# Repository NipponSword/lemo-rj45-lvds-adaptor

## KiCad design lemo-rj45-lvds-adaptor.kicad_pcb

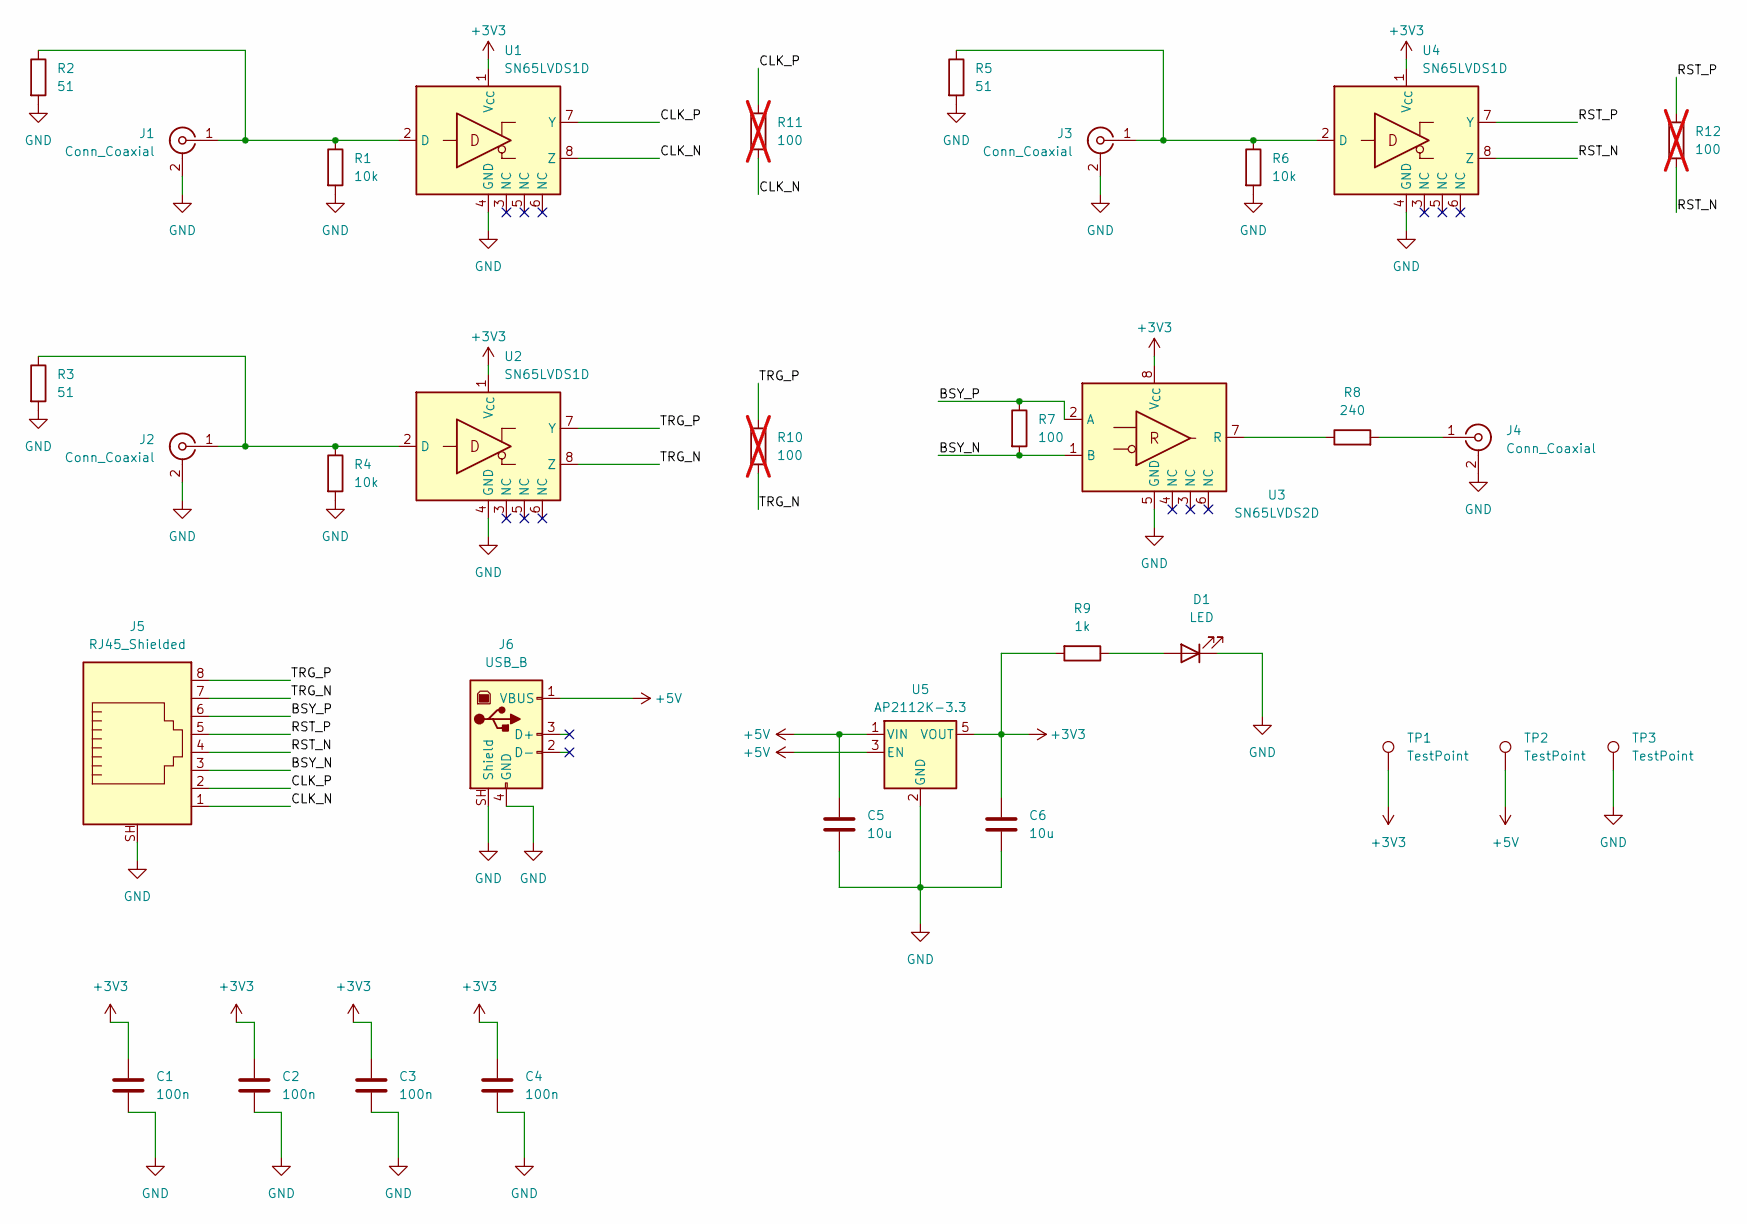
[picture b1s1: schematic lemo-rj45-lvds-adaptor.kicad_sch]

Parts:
C1, C2, C3, C4: 100n; C_0805_2012Metric_Pad1.18x1.45mm_HandSolder
C5, C6: 10u; C_0805_2012Metric_Pad1.18x1.45mm_HandSolder
D1: LED; LED_0805_2012Metric_Pad1.15x1.40mm_HandSolder
J1, J2, J3, J4: Conn_Coaxial; HS_85_QLA-01-0-2_ML97_RightAngle
J5: RJ45_Shielded; RJ45_Amphenol_RJHSE5380
J6: USB_B; USB_B_OST_USB-B1HSxx_Horizontal
R1, R4, R6: 10k; R_0805_2012Metric_Pad1.20x1.40mm_HandSolder
R2, R3, R5: 51; R_1206_3216Metric_Pad1.30x1.75mm_HandSolder
R7: 100; R_0805_2012Metric_Pad1.20x1.40mm_HandSolder
R8: 240; R_0805_2012Metric_Pad1.20x1.40mm_HandSolder
R9: 1k; R_0805_2012Metric_Pad1.20x1.40mm_HandSolder
R10, R11, R12: 100; R_0805_2012Metric_Pad1.20x1.40mm_HandSolder; not fitted
TP1, TP2, TP3: TestPoint; TestPoint_THTPad_D2.0mm_Drill1.0mm
U1, U2, U4: SN65LVDS1D; SOIC-8_3.9x4.9mm_P1.27mm
U3: SN65LVDS2D; SOIC-8_3.9x4.9mm_P1.27mm
U5: AP2112K-3.3; SOT-23-5

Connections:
+3V3: C1.1, C2.1, C3.1, C4.1, C6.1, R9.2, TP1.1, U1.1 (V_{CC}), U2.1 (V_{CC}), U3.8 (V_{CC}), U4.1 (V_{CC}), U5.5 (VOUT); also elsewhere on the board
+5V: C5.1, J6.1 (VBUS), TP2.1, U5.1 (VIN), U5.3 (EN); also elsewhere on the board
/BSY_N: J5.3, R7.2, U3.1 (B)
/BSY_P: J5.6, R7.1, U3.2 (A)
/CLK_N: J5.1, R11.2, U1.8 (Z)
/CLK_P: J5.2, R11.1, U1.7 (Y)
/RST_N: J5.4, R12.2, U4.8 (Z)
/RST_P: J5.5, R12.1, U4.7 (Y)
/TRG_N: J5.7, R10.2, U2.8 (Z)
/TRG_P: J5.8, R10.1, U2.7 (Y)
GND: C1.2, C2.2, C3.2, C4.2, C5.2, C6.2, D1.1 (K), J1.2 (Ext), J2.2 (Ext), J3.2 (Ext), J4.2 (Ext), J5.SH, J6.4 (GND), J6.SH (Shield), R1.2, R2.2, R3.2, R4.2, R5.2, R6.2, TP3.1, U1.4 (GND), U2.4 (GND), U3.5 (GND), U4.4 (GND), U5.2 (GND); also elsewhere on the board
unnamed: D1.2 (A), R9.1
unnamed: J1.1 (In), R1.1, R2.1, U1.2 (D)
unnamed: J2.1 (In), R3.1, R4.1, U2.2 (D)
unnamed: J3.1 (In), R5.1, R6.1, U4.2 (D)
unnamed: J4.1 (In), R8.2
unnamed: R8.1, U3.7 (R)

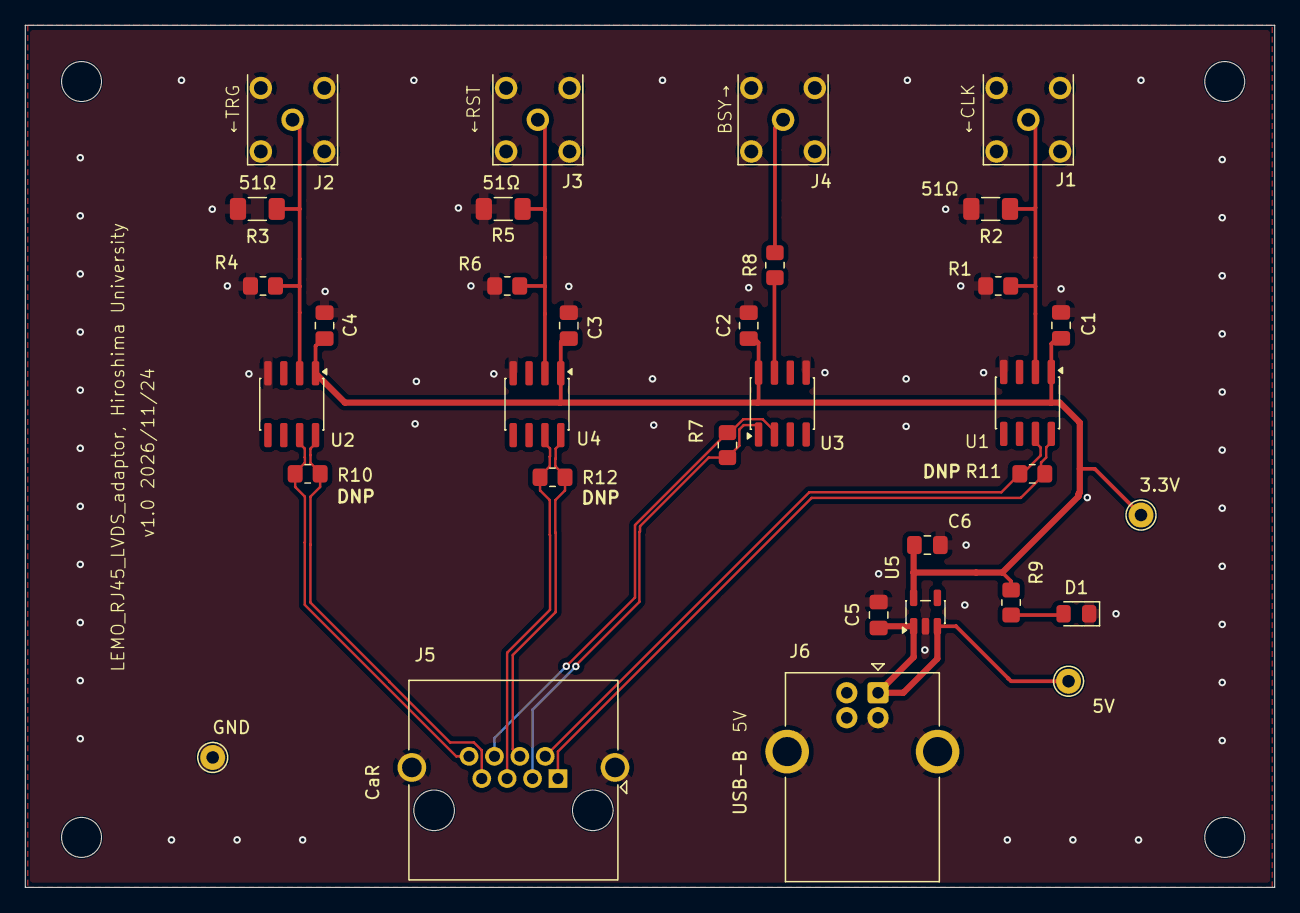
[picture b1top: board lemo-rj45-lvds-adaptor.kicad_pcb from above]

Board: 2 copper layers, 100.0 x 69.0 mm, 33 parts (0 on the bottom side), 17 nets.

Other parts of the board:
3.3V, 5V: TestPoint; TestPoint_THTPad_D2.0mm_Drill1.0mm
GND: TestPoint; TestPoint_THTPad_D2.0mm_Drill1.0mm

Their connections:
+3V3: 3.3V.1 (1_1); also elsewhere on the board
+5V: 5V.1 (1_1); also elsewhere on the board
GND: GND.1 (1_1); also elsewhere on the board
